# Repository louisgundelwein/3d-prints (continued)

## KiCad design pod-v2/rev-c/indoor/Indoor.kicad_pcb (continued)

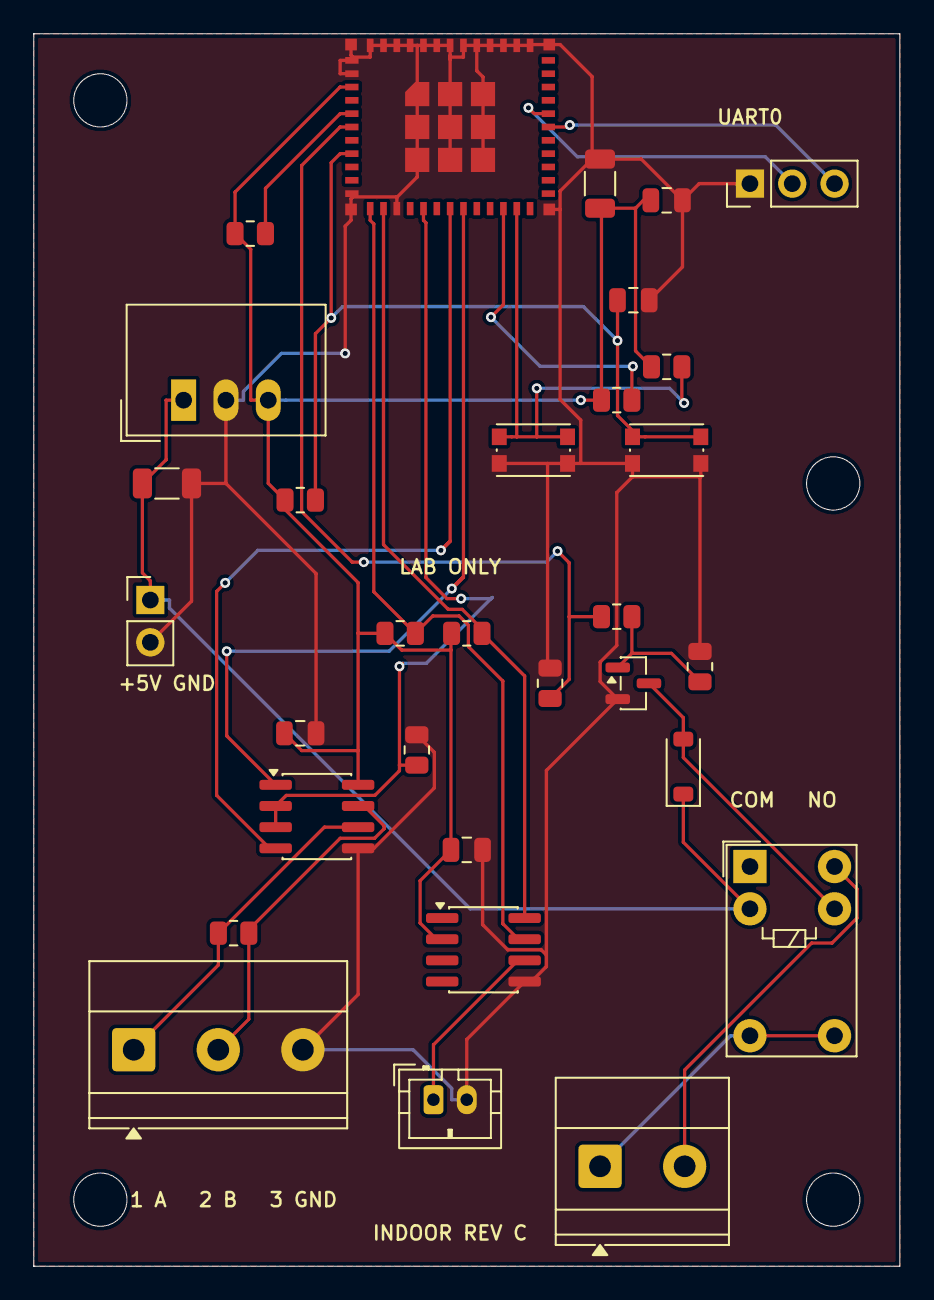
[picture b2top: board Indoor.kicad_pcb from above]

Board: 2 copper layers, 52.0 x 74.0 mm, 35 parts (0 on the bottom side), 22 nets.

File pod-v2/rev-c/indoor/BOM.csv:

Reference,Value,Footprint
J1,5V IN,Connector_PinHeader_2.54mm:PinHeader_1x02_P2.54mm_Vertical
U2,TSR 1-2433,Converter_DCDC:Converter_DCDC_TRACO_TSR-1_THT
C1,10u,Capacitor_SMD:C_1206_3216Metric
C2,10u,Capacitor_SMD:C_1206_3216Metric
C3,100n,Capacitor_SMD:C_0805_2012Metric
C4,1u,Capacitor_SMD:C_0805_2012Metric
C5,100n,Capacitor_SMD:C_0805_2012Metric
U1,ESP32-C3-MINI-1-N4X,Pod:ESP32-C3-MINI-1
R1,10k,Resistor_SMD:R_0805_2012Metric
R2,10k,Resistor_SMD:R_0805_2012Metric
R3,10k,Resistor_SMD:R_0805_2012Metric
R4,10k,Resistor_SMD:R_0805_2012Metric
SW1,BOOT,Button_Switch_SMD:SW_Push_1P1T_NO_CK_KMR2
SW2,EN,Button_Switch_SMD:SW_Push_1P1T_NO_CK_KMR2
Q1,AO3400A,Package_TO_SOT_SMD:SOT-23
R8,100,Resistor_SMD:R_0805_2012Metric
R9,10k,Resistor_SMD:R_0805_2012Metric
D2,1N4148W,Diode_SMD:D_SOD-123
K1,G5V-1 DC5,Relay_THT:Relay_SPDT_Omron_G5V-1
U3,THVD1410DR,Package_SO:SOIC-8_3.9x4.9mm_P1.27mm
R10,120,Resistor_SMD:R_0805_2012Metric
R11,10k,Resistor_SMD:R_0805_2012Metric
R12,10k,Resistor_SMD:R_0805_2012Metric
J2,RS485 A B GND,"TerminalBlock_Phoenix:TerminalBlock_Phoenix_MKDS-1,5-3-5.08_1x03_P5.08mm_Horizontal"
J3,COM NO,"TerminalBlock_Phoenix:TerminalBlock_Phoenix_MKDS-1,5-2-5.08_1x02_P5.08mm_Horizontal"
J4,UART0,Connector_PinHeader_2.54mm:PinHeader_1x03_P2.54mm_Vertical
U4,DS3231MZ+,Package_SO:SOIC-8_3.9x4.9mm_P1.27mm
C6,100n,Capacitor_SMD:C_0805_2012Metric
R13,2.2k,Resistor_SMD:R_0805_2012Metric
R14,2.2k,Resistor_SMD:R_0805_2012Metric
J5,CR2032 3V primary,Connector_JST:JST_PH_B2B-PH-K_1x02_P2.00mm_Vertical
H1,M3,MountingHole:MountingHole_3.2mm_M3
H2,M3,MountingHole:MountingHole_3.2mm_M3
H3,M3,MountingHole:MountingHole_3.2mm_M3
H4,M3,MountingHole:MountingHole_3.2mm_M3
BT1 (off-board),CR2032 3V primary nonrechargeable,Insulated cabled holder inside enclosure
J5 cable (off-board),JST PHR-2 housing + SPH-002T-P0.5S contacts,"Pin 1 battery+, pin 2 GND"
